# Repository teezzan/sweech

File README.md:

# sweech
Sweech is for switching on systems to perform certain tasks at specific time in a day, week, month or year. It performs this incredible task while ensuring the whole system remains completely off during this downtime. It helps to use very little power to control much larger power in electronic systems. 
It is a much flexible and efficient way of powersaving than  deep sleeping of MCUs since all peripheral are off most times.

Sweech is a very simple system. It uses the DS3231 for it's incredibly useful Alarm feature and extremely low power for to keeping. Sweech is basically the combination of the DS3231 and a soft switch / latch. 

The device can be communicated with using I2C. This is used for setting certain parameters such as time and alarms for the system to switch on. The whole setup runs on a coin cell. This serves as the primary source of power for Sweech during it's downtime.
The output of the board is a 5V(1A) and 3.3V(1A) pin for powering the external system. The board also contains a Vout terminal for much larger voltage(up to 30V/4A).

The plan is to make a generic board that serves most use case.  Another interesting upgrade is a version of the  board that charges the battery while also taking care of the alarm feature.

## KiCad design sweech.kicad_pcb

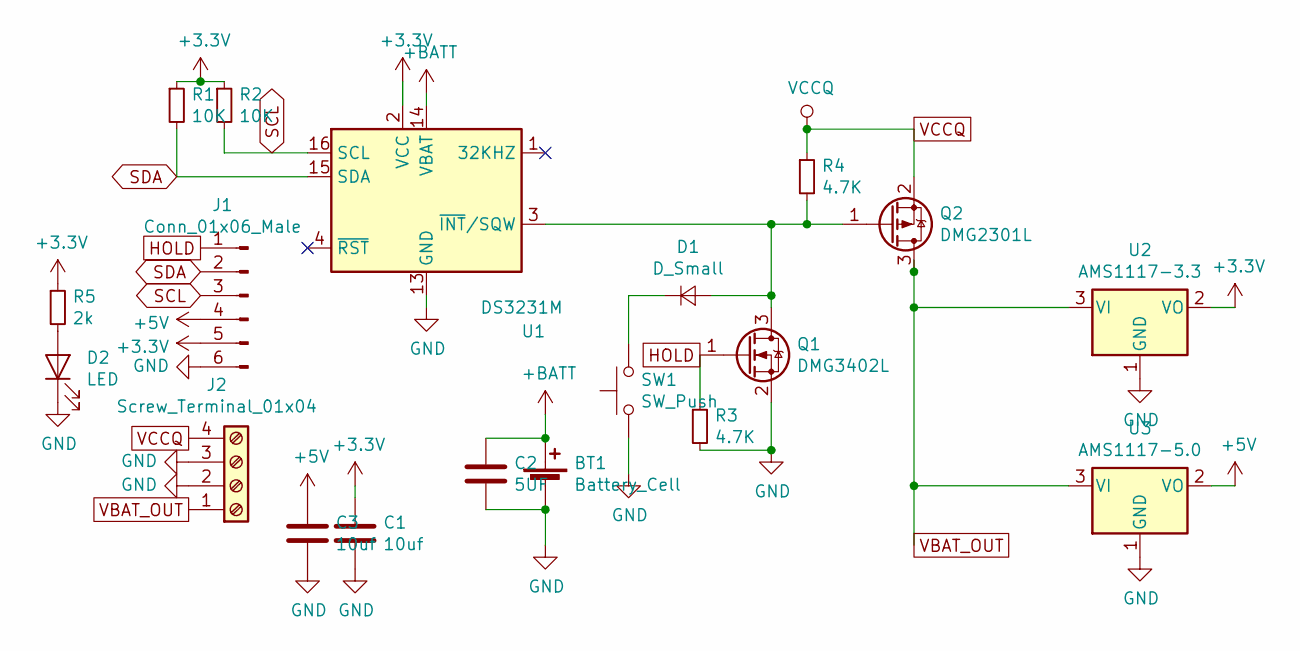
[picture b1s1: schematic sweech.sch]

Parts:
BT1: Battery_Cell; BatteryHolder_Keystone_3008_1x2450
C1, C3: 10uf; C_0603_1608Metric_Pad1.05x0.95mm_HandSolder
C2: 5UF; C_0603_1608Metric_Pad1.05x0.95mm_HandSolder
D1: D_Small; D_0603_1608Metric_Pad1.05x0.95mm_HandSolder
D2: LED; LED_0603_1608Metric
J1: Conn_01x06_Male; PinHeader_1x06_P2.54mm_Horizontal
J2: Screw_Terminal_01x04; TerminalBlock_4Ucon_1x04_P3.50mm_Vertical
Q1: DMG3402L; SOT-23
Q2: DMG2301L; SOT-23
R1, R2: 10K; R_0603_1608Metric_Pad1.05x0.95mm_HandSolder
R3, R4: 4.7K; R_0603_1608Metric_Pad1.05x0.95mm_HandSolder
R5: 2k; R_0603_1608Metric_Pad1.05x0.95mm_HandSolder
SW1: SW_Push; SW_SPST_PTS645
U1: DS3231M; SOIC-16W_7.5x10.3mm_P1.27mm
U2: AMS1117-3.3; SOT-223-3_TabPin2
U3: AMS1117-5.0; SOT-223-3_TabPin2

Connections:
+3V3: C1.1, J1.5, R1.1, R2.1, R5.1, U1.2 (VCC), U2.2 (VO)
+5V: C3.1, J1.4, U3.2 (VO)
+BATT: BT1.1 (+), C2.1, U1.14 (VBAT)
GND: BT1.2 (-), C1.2, C2.2, C3.2, D2.1 (K), J1.6, J2.2, J2.3, Q1.2 (S), R3.2, SW1.1, U1.5 (GND), U1.6 (GND), U1.7 (GND), U1.8 (GND), U1.9 (GND), U1.10 (GND), U1.11 (GND), U1.12 (GND), U1.13 (GND), U2.1 (GND), U3.1 (GND)
HOLD: J1.1, Q1.1 (G), R3.1
unnamed: D1.1 (K), SW1.2
unnamed: D1.2 (A), Q1.3 (D), Q2.1 (G), R4.2, U1.3 (~INT~/SQW)
unnamed: D2.2 (A), R5.2
SCL: J1.3, R2.2, U1.16 (SCL)
SDA: J1.2, R1.2, U1.15 (SDA)
VBAT_OUT: J2.1, Q2.3 (D), U2.3 (VI), U3.3 (VI)
VCCQ: J2.4, Q2.2 (S), R4.1

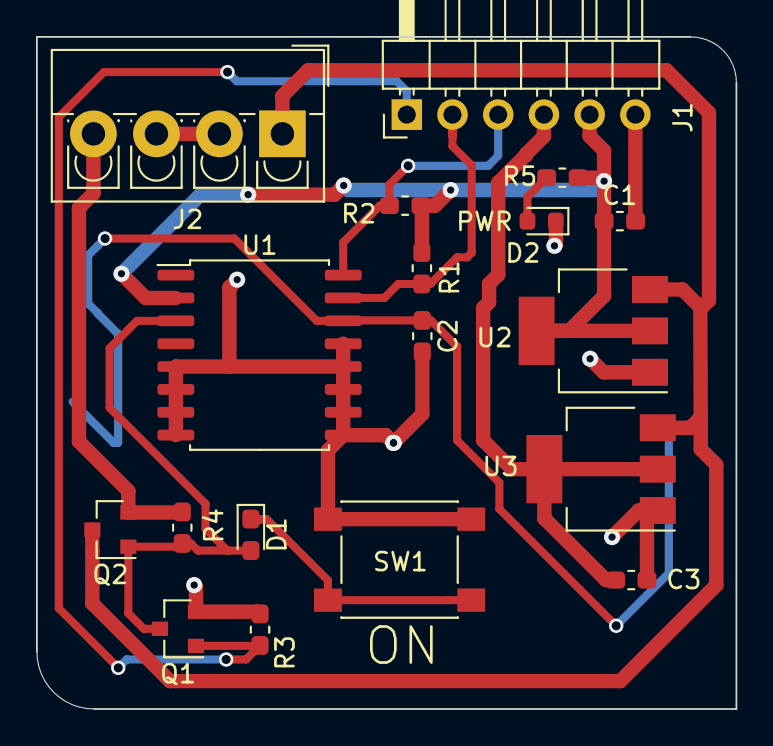
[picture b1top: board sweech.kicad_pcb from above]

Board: 2 copper layers, 38.9 x 37.3 mm, 19 parts (1 on the bottom side), 12 nets.

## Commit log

2020-04-27 Created README
